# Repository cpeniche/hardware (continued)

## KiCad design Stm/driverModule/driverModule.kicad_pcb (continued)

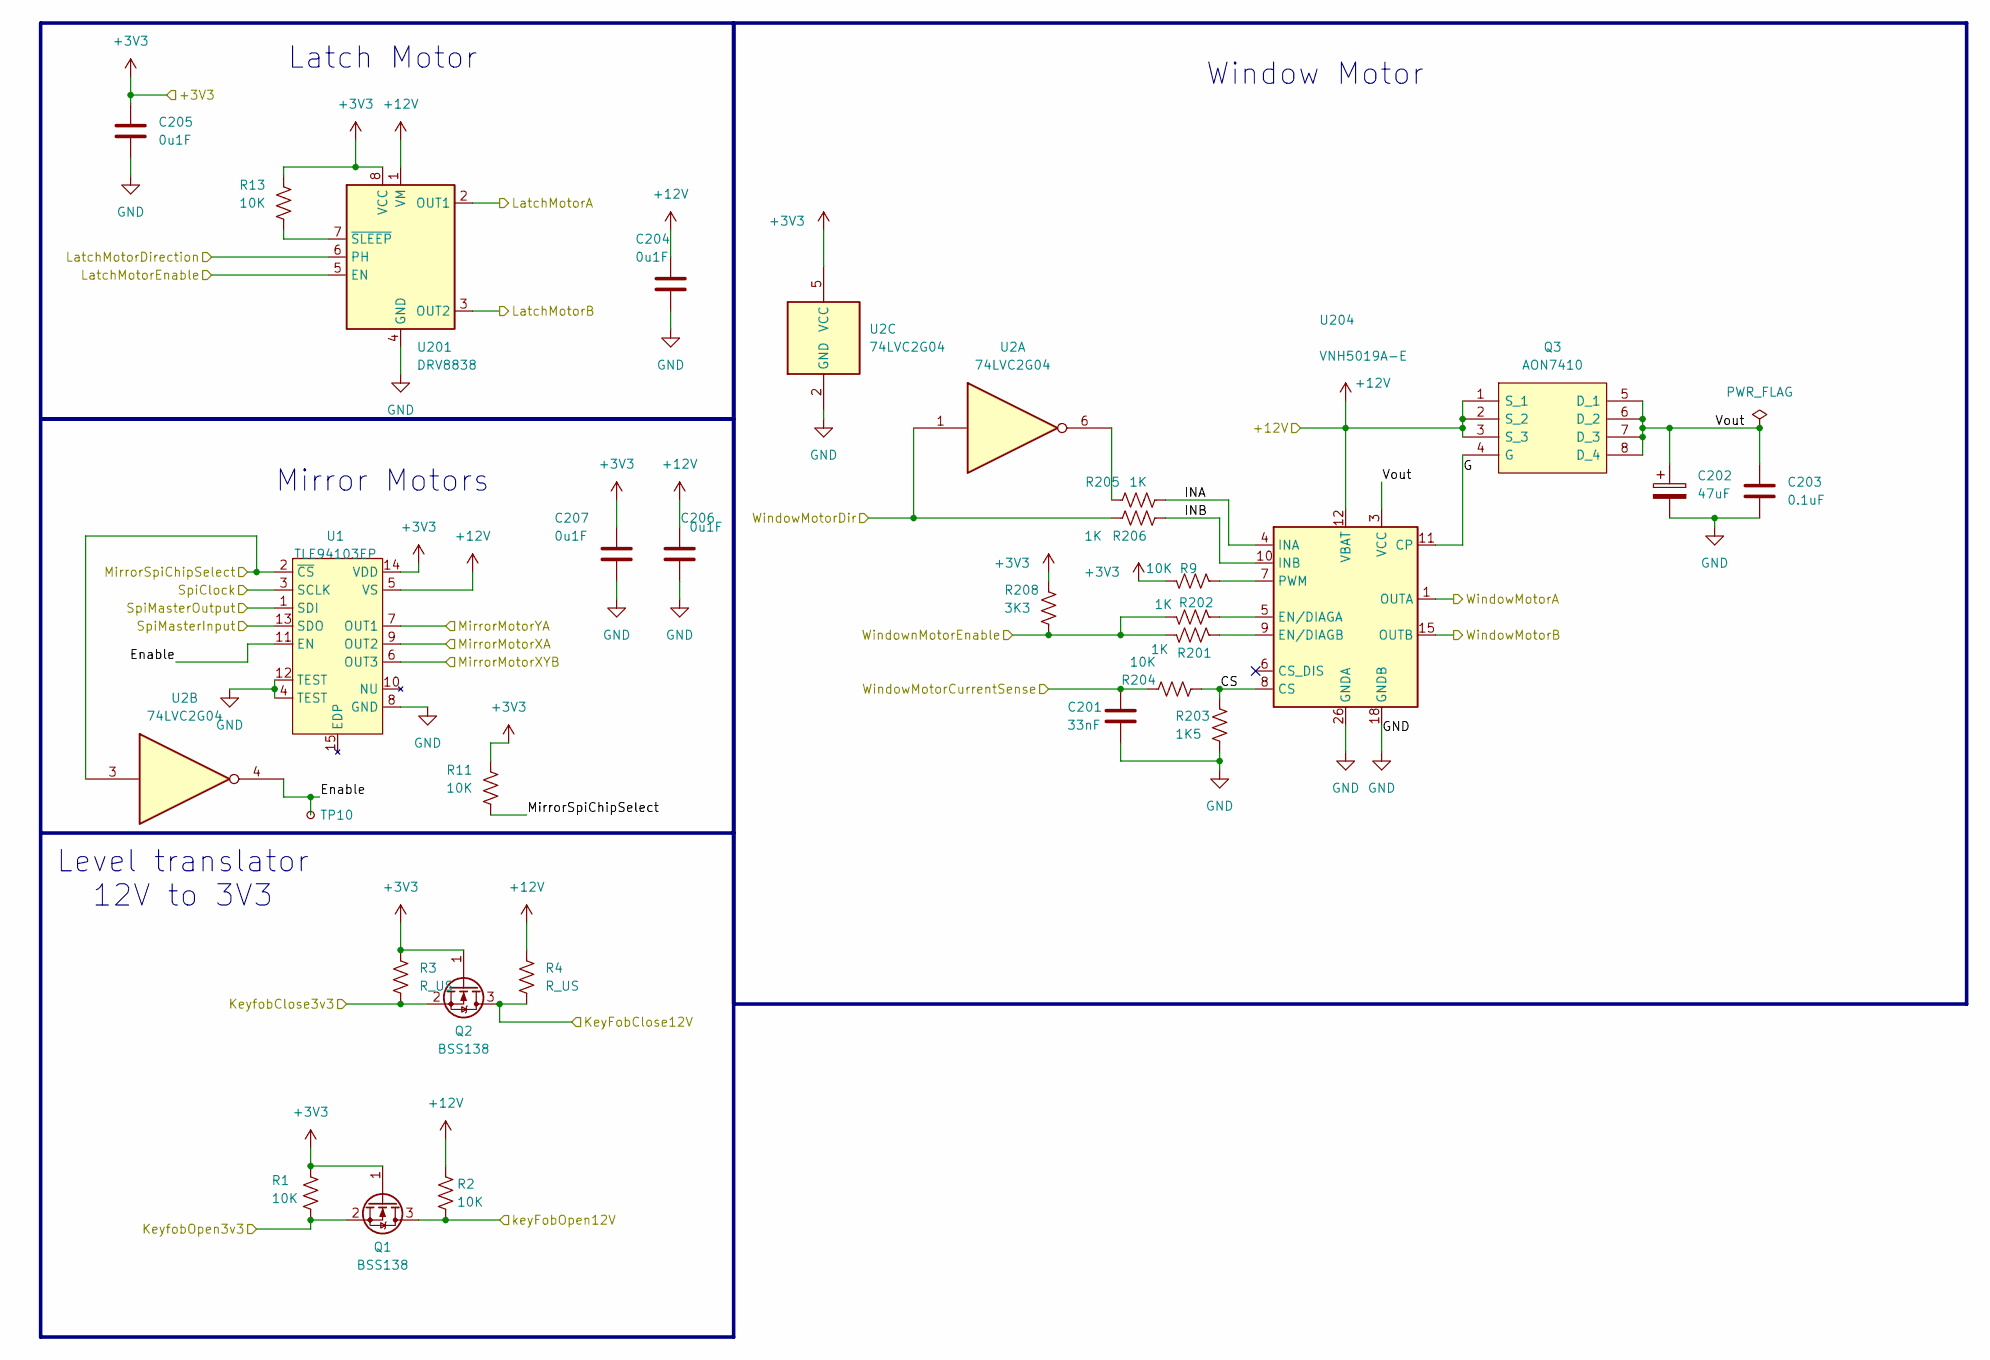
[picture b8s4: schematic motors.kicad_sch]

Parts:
C201: 33nF; C_0805_2012Metric
C202: 47uF; CP_EIA-6032-15_Kemet-U
C203: 0.1uF; C_0402_1005Metric_Pad0.74x0.62mm_HandSolder
C204, C205, C206, C207: 0u1F; C_0402_1005Metric_Pad0.74x0.62mm_HandSolder
Q1, Q2: BSS138; SOT-23
Q3: AON7410; DFN_3X3_EP; Manufacturer_Part_Number AON7410
R1, R2, R9, R11, R13, R204: 10K; R_0402_1005Metric_Pad0.72x0.64mm_HandSolder
R3, R4: R_US; R_0402_1005Metric_Pad0.72x0.64mm_HandSolder
R201, R202, R205, R206: 1K; R_0402_1005Metric_Pad0.72x0.64mm_HandSolder
R203: 1K5; R_0402_1005Metric_Pad0.72x0.64mm_HandSolder
R208: 3K3; R_0402_1005Metric_Pad0.72x0.64mm_HandSolder
TP10: TestPoint_Small; TestPoint_Pad_1.0x1.0mm
U1: TLE94103EP; Infineon_PG-TSDSO-14-22
U2: 74LVC2G04; SOT-363_SC-70-6
U201: DRV8838; WSON-8-1EP_2x2mm_P0.5mm_EP0.9x1.6mm
U204: VNH5019A-E; ST_MultiPowerSO-30

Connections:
+3V3: C205.1, C207.1, Q1.1 (G), Q2.1 (G), R1.1, R3.1, R9.1, R11.1, R13.1, R208.1, U1.14 (VDD), U2.5 (VCC), U201.8 (VCC); also elsewhere on the board
+12V: C204.1, C206.1, Q3.1 (S_1), Q3.2 (S_2), Q3.3 (S_3), R2.1, R4.1, U1.5 (VS), U201.1 (VM), U204.12 (VBAT); also elsewhere on the board
/Harness/KeyFobClose12V: Q2.3 (D), R4.2; also elsewhere on the board
/Harness/LatchMotorA: U201.2 (OUT1); also elsewhere on the board
/Harness/LatchMotorB: U201.3 (OUT2); also elsewhere on the board
/Harness/MirrorMotorXA: U1.7 (OUT1); also elsewhere on the board
/Harness/MirrorMotorXYB: U1.6 (OUT3); also elsewhere on the board
/Harness/MirrorMotorYA: U1.9 (OUT2); also elsewhere on the board
/Harness/WindowMotorA: U204.1 (OUTA), U204.25 (OUTA), U204.30 (OUTA), U204.33 (OUTA); also elsewhere on the board
/Harness/WindowMotorB: U204.15 (OUTB), U204.16 (OUTB), U204.21 (OUTB), U204.32 (OUTB); also elsewhere on the board
/Harness/keyFobOpen12V: Q1.3 (D), R2.2; also elsewhere on the board
/KeyfobClose3v3: Q2.2 (S), R3.2; also elsewhere on the board
/KeyfobOpen3v3: Q1.2 (S), R1.2; also elsewhere on the board
/LatchMotorDirection: U201.6 (PH); also elsewhere on the board
/LatchMotorEnable: U201.5 (EN); also elsewhere on the board
/MirrorSpiChipSelect: R11.2, U1.2 (~CS), U2.3; also elsewhere on the board
/Motors Interface/CS: R203.1, R204.2, U204.8 (CS)
/Motors Interface/Enable: TP10.1, U1.11 (EN), U2.4
/Motors Interface/G: Q3.4 (G), U204.11 (CP)
/Motors Interface/INA: R205.2, U204.4 (INA)
/Motors Interface/INB: R206.2, U204.10 (INB)
/Motors Interface/Vout: C202.1, C203.1, Q3.5 (D_1), Q3.6 (D_2), Q3.7 (D_3), Q3.8 (D_4), U204.3 (VCC), U204.13 (VCC), U204.23 (VCC), U204.31 (VCC)
/SpiClock: U1.3 (SCLK); also elsewhere on the board
/SpiMasterInput: U1.13 (SDO); also elsewhere on the board
/SpiMasterOutput: U1.1 (SDI); also elsewhere on the board
/WindowMotorCurrentSense: C201.1, R204.1; also elsewhere on the board
/WindowMotorDir: R206.1, U2.1; also elsewhere on the board
/WindowMotorEnable: R201.1, R202.1, R208.2; also elsewhere on the board
GND: C201.2, C202.2, C203.2, C204.2, C205.2, C206.2, C207.2, R203.2, U1.4 (TEST), U1.8 (GND), U1.12 (TEST), U2.2 (GND), U201.4 (GND), U201.9 (GND), U204.18 (GNDB), U204.19 (GNDB), U204.20 (GNDB), U204.26 (GNDA), U204.27 (GNDA), U204.28 (GNDA); also elsewhere on the board
unnamed: R205.1, U2.6
unnamed: R13.2, U201.7 (~SLEEP)
unnamed: R202.2, U204.5 (EN/DIAGA)
unnamed: R201.2, U204.9 (EN/DIAGB)
unnamed: R9.2, U204.7 (PWM)

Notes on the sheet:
Level translator 12V to 3V3
Mirror Motors
Latch Motor
Window Motor

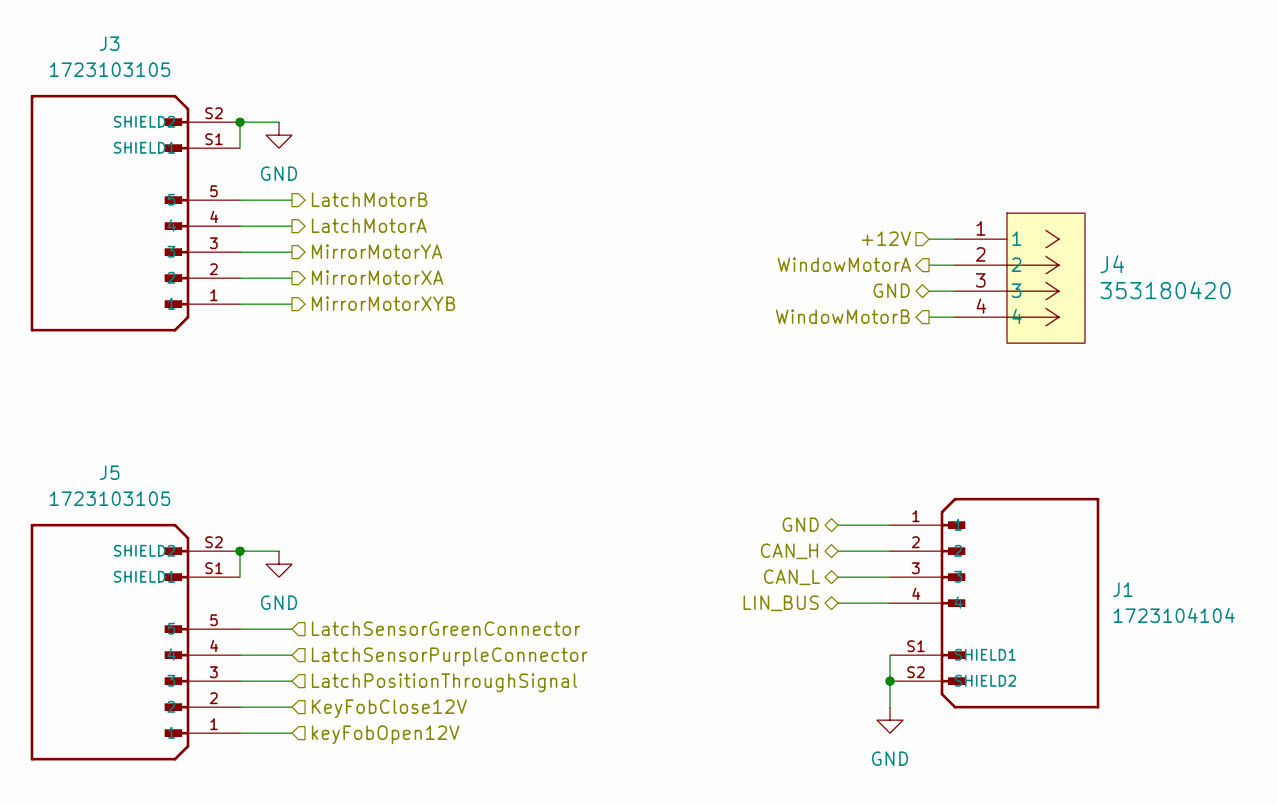
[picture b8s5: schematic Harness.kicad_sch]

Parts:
J1: 1723104104; MOLEX_1723104104; PARTREV with Solder Nail, 3.50mm Pitch, Single 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
J3, J5: 1723103105; MOLEX_1723103105; PARTREV B1
J4: 353180420; CONN_35318-0420_MOL

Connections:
+12V: J4.1; also elsewhere on the board
/CAN_H: J1.2; also elsewhere on the board
/CAN_L: J1.3; also elsewhere on the board
/Harness/KeyFobClose12V: J5.2; also elsewhere on the board
/Harness/LatchMotorA: J3.4; also elsewhere on the board
/Harness/LatchMotorB: J3.5; also elsewhere on the board
/Harness/MirrorMotorXA: J3.2; also elsewhere on the board
/Harness/MirrorMotorXYB: J3.1; also elsewhere on the board
/Harness/MirrorMotorYA: J3.3; also elsewhere on the board
/Harness/WindowMotorA: J4.2; also elsewhere on the board
/Harness/WindowMotorB: J4.4; also elsewhere on the board
/Harness/keyFobOpen12V: J5.1; also elsewhere on the board
/LIN_BUS: J1.4; also elsewhere on the board
/LatchPositionThroughSignal: J5.3; also elsewhere on the board
/LatchSensorGreenConnector: J5.4; also elsewhere on the board
/LatchSensorPurpleConnector: J5.5; also elsewhere on the board
GND: J1.1, J1.S1 (SHIELD1), J1.S2 (SHIELD2), J3.S1 (SHIELD1), J3.S2 (SHIELD2), J4.3, J5.S1 (SHIELD1), J5.S2 (SHIELD2); also elsewhere on the board

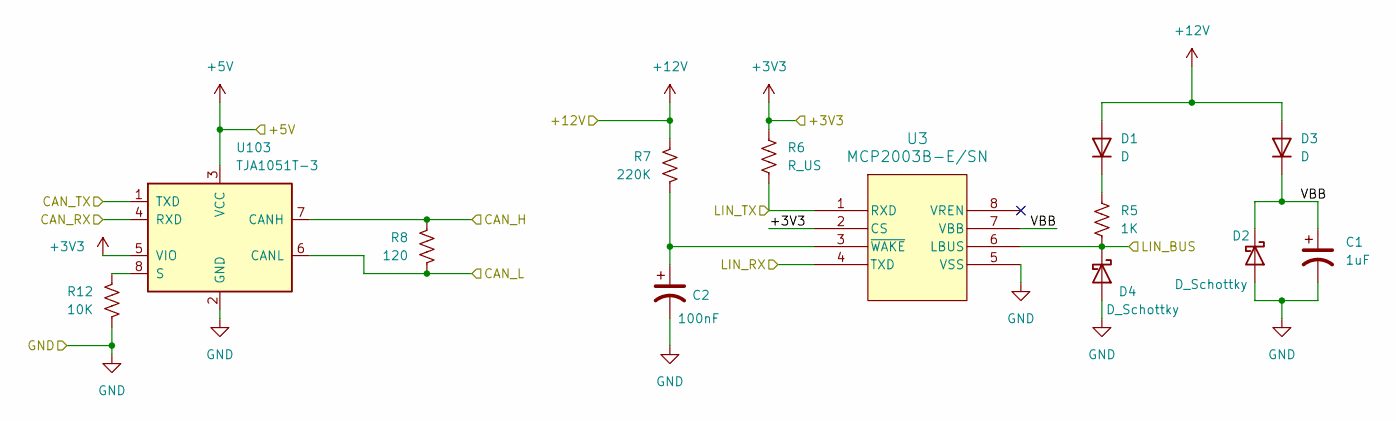
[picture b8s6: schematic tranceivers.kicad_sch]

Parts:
C1: 1uF; C_0402_1005Metric
C2: 100nF; C_0402_1005Metric
D1, D3: D; D_0402_1005Metric
D2, D4: D_Schottky; D_0402_1005Metric
R5: 1K; R_0402_1005Metric
R6: R_US; R_0402_1005Metric
R7: 220K; R_0402_1005Metric
R8: 120; R_0402_1005Metric
R12: 10K; R_0402_1005Metric
U3: MCP2003B-E/SN; SOIC8_SN_MCH
U103: TJA1051T-3; SOIC-8_3.9x4.9mm_P1.27mm

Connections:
+3V3: R6.1, U3.2 (CS), U103.5 (VIO); also elsewhere on the board
+5V: U103.3 (VCC); also elsewhere on the board
+12V: D1.2 (A), D3.2 (A), R7.1; also elsewhere on the board
/CAN_H: R8.1, U103.7 (CANH); also elsewhere on the board
/CAN_L: R8.2, U103.6 (CANL); also elsewhere on the board
/CAN_RX: U103.1 (TXD); also elsewhere on the board
/CAN_TX: U103.4 (RXD); also elsewhere on the board
/LIN_BUS: D4.1 (K), R5.2, U3.6 (LBUS); also elsewhere on the board
/LIN_RX: U3.4 (TXD); also elsewhere on the board
/LIN_TX: R6.2, U3.1 (RXD); also elsewhere on the board
/Transceivers/VBB: C1.1, D2.1 (K), D3.1 (K), U3.7 (VBB)
GND: C1.2, C2.2, D2.2 (A), D4.2 (A), R12.2, U3.5 (VSS), U103.2 (GND); also elsewhere on the board
unnamed: D1.1 (K), R5.1
unnamed: C2.1, R7.2, U3.3 (~WAKE)
unnamed: R12.1, U103.8 (S)

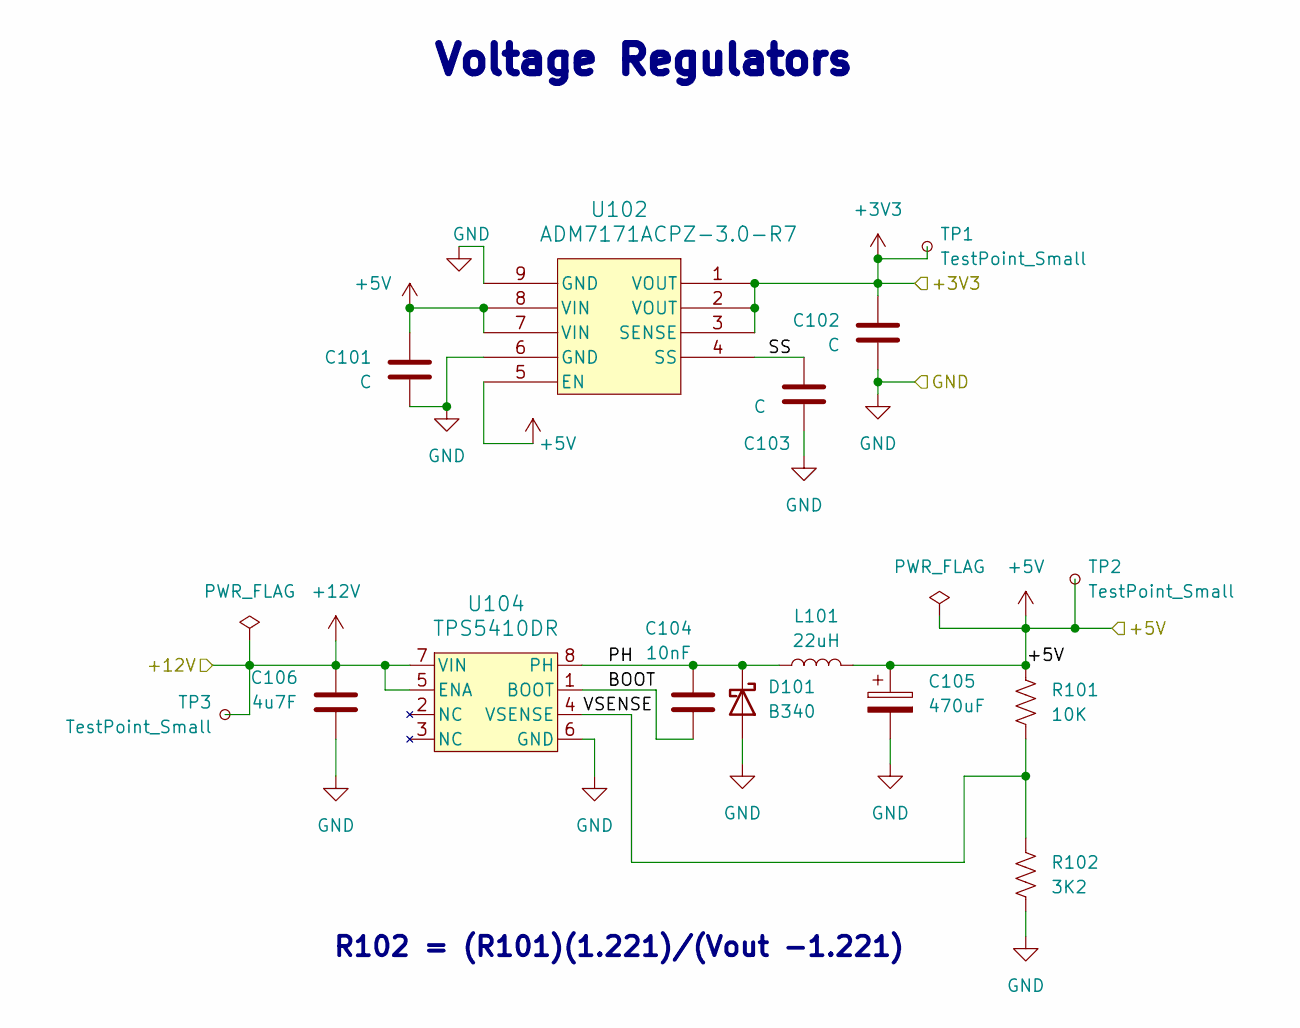
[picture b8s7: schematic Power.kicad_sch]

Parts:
C101, C102, C103: C; C_0402_1005Metric_Pad0.74x0.62mm_HandSolder
C104: 10nF; C_0805_2012Metric
C105: 470uF; CP_EIA-7132-20_AVX-U
C106: 4u7F; C_0805_2012Metric
D101: B340; D_SMC
L101: 22uH; L-SMD-13.45x12.6X5.0mm
R101: 10K; R_0402_1005Metric_Pad0.72x0.64mm_HandSolder
R102: 3K2; R_0402_1005Metric_Pad0.72x0.64mm_HandSolder
TP1, TP2, TP3: TestPoint_Small; TestPoint_Pad_1.0x1.0mm
U102: ADM7171ACPZ-3.0-R7; LFCSP-8-1EP_3x3mm_P0.5mm_EP_1.70x2.54mm
U104: TPS5410DR; SOIC-8-1EP_3.9x4.9mm_P1.27mm

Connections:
+3V3: C102.1, TP1.1, U102.1 (VOUT), U102.2 (VOUT), U102.3 (SENSE); also elsewhere on the board
+5V: C101.1, C105.1, L101.2, R101.1, TP2.1, U102.5 (EN), U102.7 (VIN), U102.8 (VIN); also elsewhere on the board
+12V: C106.2, TP3.1, U104.5 (ENA), U104.7 (VIN); also elsewhere on the board
/Power/BOOT: C104.1, U104.1 (BOOT)
/Power/PH: C104.2, D101.1 (K), L101.1, U104.8 (PH)
/Power/SS: C103.1, U102.4 (SS)
/Power/VSENSE: R101.2, R102.1, U104.4 (VSENSE)
GND: C101.2, C102.2, C103.2, C105.2, C106.1, D101.2 (A), R102.2, U102.6 (GND), U102.9 (GND), U104.6 (GND); also elsewhere on the board

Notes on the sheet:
R102 = (R101)(1.221)/(Vout -1.221)
Voltage Regulators

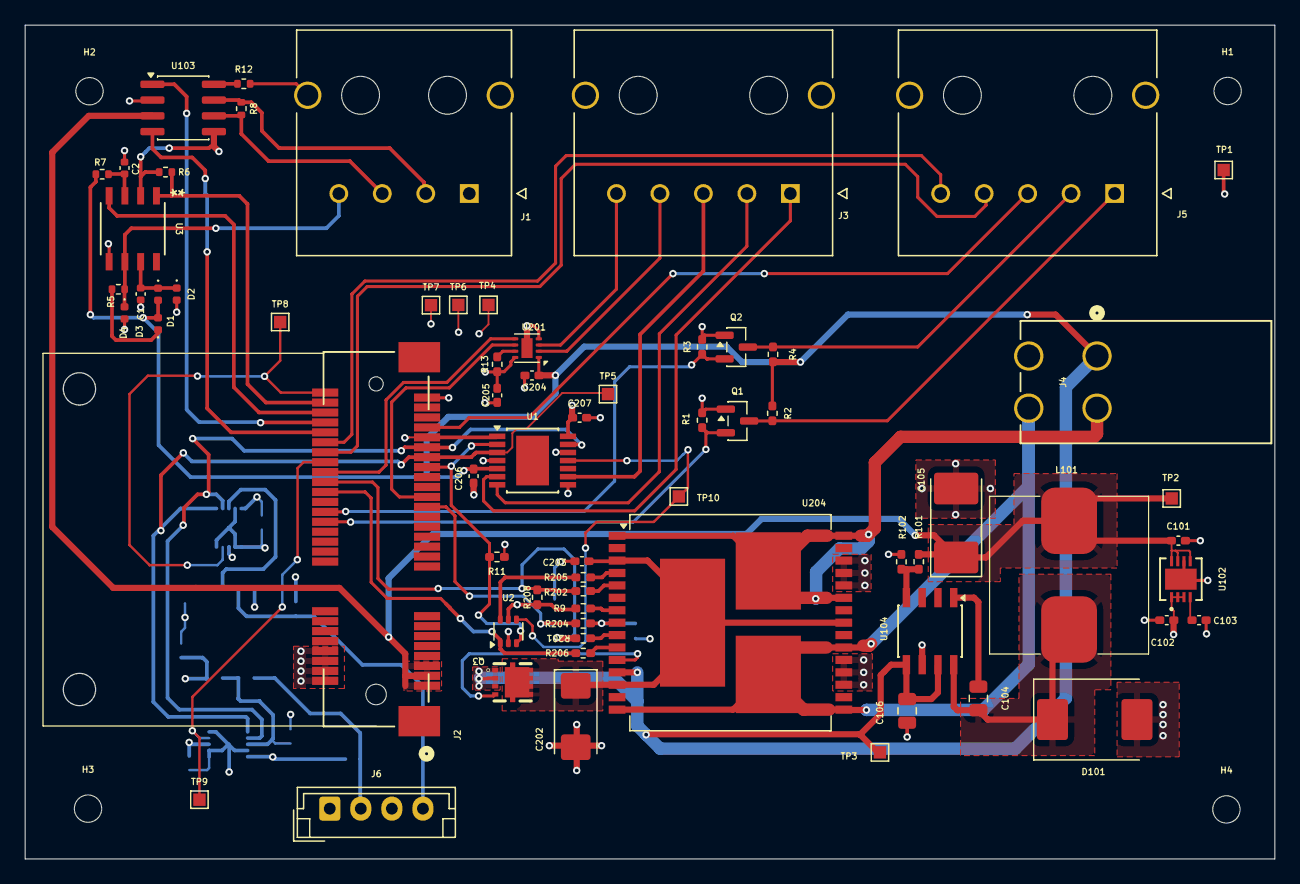
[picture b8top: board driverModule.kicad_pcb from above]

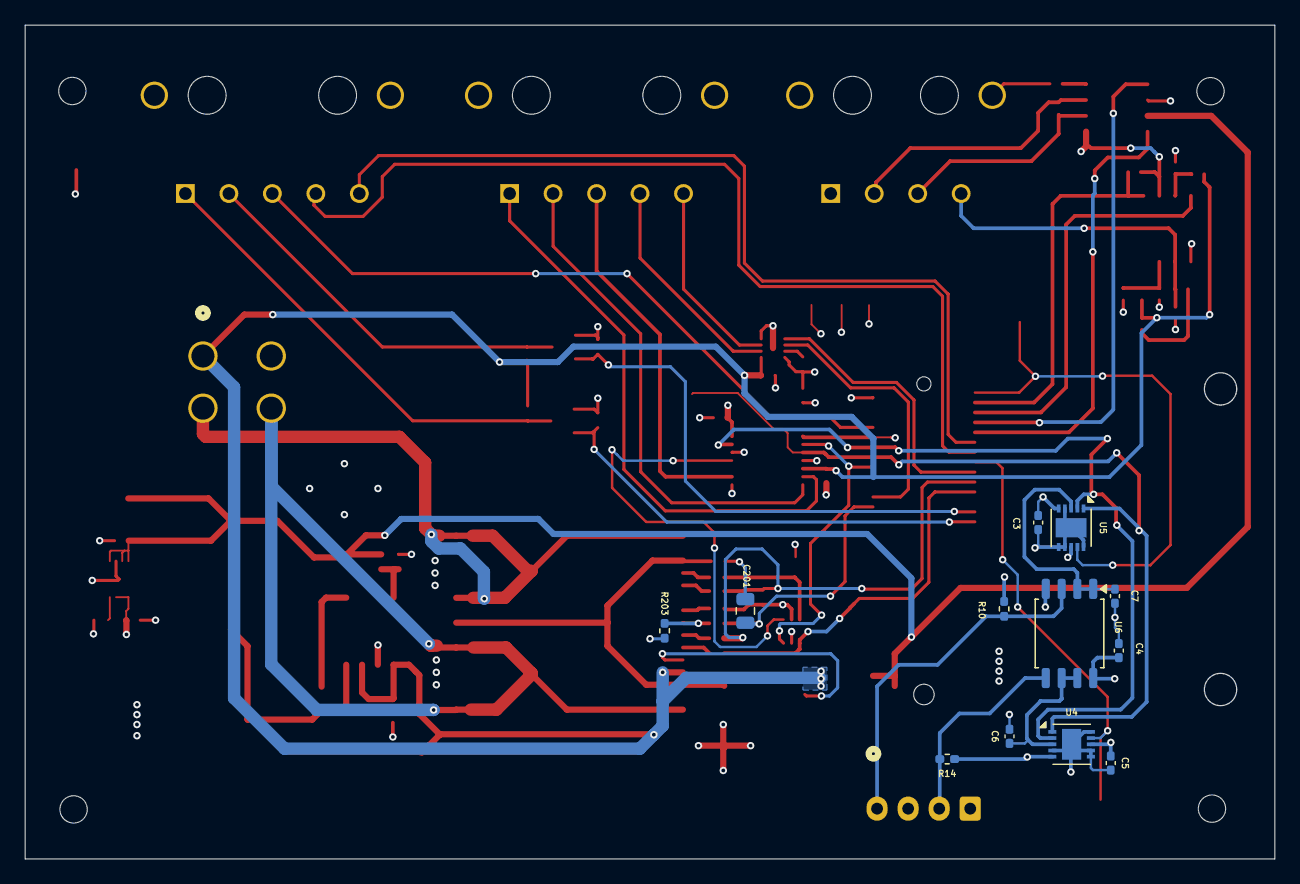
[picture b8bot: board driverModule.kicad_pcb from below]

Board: 4 copper layers, 100.6 x 67.1 mm, 83 parts (12 on the bottom side), 59 nets.

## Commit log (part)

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2022-03-04 Changed folders
2022-03-04 first revision
    Added 3dparty libraries
2022-03-04 libraries
    Added more libraries
2024-03-13 Add more Project
    Add Arduino hat and Stm32f767 project
2024-03-22 LPC1788_SOM
2024-03-22 Memory connections
2024-03-25 Add sodim connector
2024-03-25 update gitignore
2024-03-25 More connections
2024-06-20 Driver Module Hardware
2024-06-21 Add Headers
2024-06-24 CD40109BNSR
    Added low to high level shifter
    and foot print
2024-06-25 Mirror Motors and key fob
    Changed for a 3 half bridge semiconductor
    Added level shift translator for key fob input
2024-06-25 LPC1788
    Added LPC1788 som module
2024-06-25 Connector
    Removed processor and add a two SMD connectors to plug a MCU carrier board
    Generate first Printed Circuit board layout
2024-06-27 Shift Registers
    Changed shift registers to mc74hc165
2024-06-28 Symbols
    Changed some symbols
    Components placements
2024-06-28 3d Models
    Added Some 3d Models
    And remove some components from schematic
2024-06-28 Esp32-s3
    Initial creation of the carrier module for the esp32-s3
2024-07-01 Carrier Board
    Added Carrier board for the ESP32-XIAO Board
2024-07-01 Routing
    Finish some routing
2024-07-01 Connectors
    Added connector symbols and 3d views
2024-07-01 Connector
    Modify jst connector (Need to look for the correct One)
2024-07-17 Submodule
    Added Sparkfun libraries and footprints
2024-07-31 Remove Connector
2024-08-01 Changed Connector
2024-08-05 PCB Board
    PCB board created, need to verify connectors polarity
2024-08-06 3d Symbols
    Update 3d symbols
2024-09-05 Agilent SPS
2025-07-10 Initial Revision
    Added S3 Wroom-2 carrier board to github
2025-07-10 Unused library formats
    Removed old Kicad symbol libraries
2025-07-10 Rename
    rename user libraries
2025-07-10 Power sheet
    Added Esp32 power sheet and rename previous sheets
2025-07-11 Connectors
    Lower connector routed
2025-07-11 Symbols
    Added New symbols
2025-07-11 Routing
    Routing finished needs to be verify
2025-07-18 database
    Create database library file
2025-07-18 libraries
    Added new libraries
2025-07-18 two layer board
    Final 2 layer board
2025-07-18 libraries
    Add connector DF9B-25S
2025-07-18 Connectors
    change one connector from 21 to 25 pins
    Added test points
2025-07-30 Sprinkler
    Added ESP8266 sprinkler board
2025-07-30 Database
    Add test files for Database implementation
2025-07-30 New Symbols
    added m.2 card symbols and footprint
2025-07-30 New sheets
    Added power sheet and micro controller sheet
2025-07-31 Library
    Added new miscellaneous parts, footprints and 3D viewers.
2025-07-31 Esp8266
    Created a new esp-wroom carrier board
2025-07-31 Sprinklers
    Added RTC and valver drivers modules for the Sprinklers
2025-08-01 Library
    Added New libraries symbols and footprints
2025-08-01 microcontroller
    Wire micro controller pin out to connector
2025-08-04 Board Layout
    Changed board layout to something smaller
2025-08-05 capacitor layout
    Changed capacitor position to front layer to have enough clearance on bottom layer
2025-08-11 Symblols
    added new symbols to library
2025-08-11 Transistor changes
    Changed all Bjt transistors to Mosfets
    Assign footprints
2025-08-12 Labraries
    Added New symbols to Kicad library
2025-08-12 Update connections
    Connect Micro controller inputs and outputs
2025-08-14 symbols
    Add terminal block connector
2025-08-14 Documentation
    Added Documentation folder
2025-08-14 pcb
    First component layout (need to verify ESP8266 board size for fitment)
2025-08-15 Traces
    Layout traces for the PCB
2025-08-18 holes
    Adding mounting holes
2025-11-04 Create stm32g431kb module
2025-11-05 Libraries
    Add Mini PCI Express half card component and update some libraries descriptions
2025-11-05 PCB
    Create pcb
2025-11-06 libraries
    Add description to some libraries
2025-11-06 Pcb
    Add more components
2025-11-07 libraries
    Added new crystal oscillator
2025-11-07 SOM
    Added Card Holes, Needed?
2025-11-08 libraries
    Added usb connector, crystal
2025-11-08 Pcb
    Pre-final PCB
2025-11-10 libraries
    Add mini PCI Express Board connector and add LIN Bus transceiver chip
2025-11-11 Driver Board
    Modify driver module for the PCI express cpu card
2025-11-11 CPU Card
    Specified not connected pins in the schematic
2025-11-11 library
    Changed PCI express connector symbol
2025-11-11 Connector
    Connect all missing inputs and outputs
2025-11-12 Libraries
    Added Molex Mini50 Automotive connector
2025-11-12 Connectors
    Remove some enable signals
    Added Harness connectors
2026-01-01 Update
    Add connection to the harness
2026-01-08 libraries
    Add new molex connectors
2026-01-08 Directories
    Update 3d model directory
2026-01-12 libraries
    Add foot print to libraries
2026-01-12 routing
    Finished PCB routing
2026-01-19 libraries
    Added libraries and 3d models
2026-01-19 Board layout
    Corrected footprints to use 0402
2026-01-19 BOM
    added html bill of materials
2026-01-28 routing
    Update board routing
2026-01-28 Libraries
    Modify some libraries
2026-01-29 library
    Update description
2026-01-29 Pcie Breakout Board
    Create a breakout board for the PCI express card
2026-01-29 PCI Express
    Create breakout board for the PCI express mini card half
2026-01-30 library
    Added ad7171 symbol
2026-01-30 ADC
    Added adc to read passenger input signals
2026-02-03 Capacitors
    Added some filter capacitors
2026-02-06 Small modifications
2026-02-07 Nordic
    added Nordic 52840 board
2026-02-07 Library
    Added NRF52840 symbol
2026-02-07 Update
    Update descriptions
2026-02-07 Fabrication Files
    Added relative directory for fabrication Files
    added fabrication files
2026-02-10 Library
    Added FFC,FPC connector
2026-02-10 pci express Breakoutt Board
    Finished routing
2026-02-13 dirctories
    Add and remove directories
2026-02-19 Libraries
    Add new motor control symbol and inductor
2026-02-19 mpq6524
    Added new breakout board for the MPQ6524 Quad half bridge motor controller
2026-02-20 Paths
    Route some paths
2026-02-20 Motor connector
    Add motor connector
2026-03-03 Connector
    Added Jst Connector 4 position
2026-03-03 Motor connector
    added smd connector for the motor outputs
2026-03-13 footprints
    Update capacitor footprints
2026-03-13 3d models
    Create 3d Models
2026-03-14 traces
    Make traces thicker
2026-03-16 library
    added MP6612G Motor Driver
2026-03-16 MP6612 Board
    Create new board for the MP6612 Motor controller
2026-03-17 libraries
    Add new terminal block and update 3d model connectors
2026-03-17 Layout
    Update layouts for the motor drivers
2026-03-18 library
    added diode footprint
2026-03-18 Rename Project
    Rename project to MP6612
2026-03-20 library
    Added 32 Mhz crystal component
2026-03-20 projects
    Update projects
2026-03-24 library
    added antenna component
2026-03-24 antenna
    Implementing antenna layout
2026-03-24 Design
    adding Nordic semiconductor reference design example
2026-03-24 library
    Added NRF52840 3d model
2026-03-24 layout
    changed Layout
2026-03-25 Update
    Change some footprints and update RF trace
